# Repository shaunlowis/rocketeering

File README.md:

# rocketeering
Documentation, progress and updates added [here](https://shaunlowis.github.io/rocketeering/)

NOTE: This guide, code, information and its authors assume no liability for outcomes or results of its use or distribution. All code and information is provided as-is for education purposes.

# Setup

Download appropriate version from [here](https://sourceforge.net/projects/sdcc/)

## Ubuntu

If on ubuntu, you should already have gcc and some form of python.

```
cd path-to-download

tar xjf sdcc-<some-version>.tar.bz

cd sdcc-<some-version>

# this will contain another file with the same name, move to that:
cd sdcc-<some-version>

# then run:
sudo ./configure

# you will probably have some missing dependencies, which I just installed with:
sudo apt install bison
sudo apt install flex
sudo apt install gputils

# repeat above until all requirements are met
# this will take quite a long time
make

# slightly faster
sudo make install

# if all went well:
sdcc -v

# which outputs something like:
SDCC : mcs51/z80/z180/r2k/r2ka/r3ka/sm83/tlcs90/ez80_z80/z80n/r800/ds390/pic16/pic14/TININative/ds400/hc08/s08/stm8/pdk13/pdk14/pdk15/mos6502/mos65c02 TD- 4.4.0 #14620 (Linux)
published under GNU General Public License (GPL)
```

Note; semi-useful guide on SDCC, see [here](https://martyn.welchs.me.uk/posts/installing-and-using-sdcc-on-linux/). For a more comprehensive guide, see the [user manual](https://sdcc.sourceforge.net/doc/sdccman.pdf).

Now we need to install the STM8 flash setup. I assume you have an ST-Link debugger, with a SWIM capable interface.
```
# wherever you want the repo to be
git clone https://github.com/vdudouyt/stm8flash.git

cd stm8flash

# dependencies:
sudo apt-get install pkg-config libusb-1.0-0-dev

make

sudo make install
```

### Download standard library
Source files for the STM8S Standard Peripheral Library are available from ST,
but it is more recommended to get the patched files from [here](https://github.com/roshbaby/stm8s-sdcc). Some further adjustments are required, depending on the
specific STM8 you have.

### Wiring the STLINK
We are using the STLINK-V2. The STM8 micro has to be debugged over SWIM.

Details for this are in section 7.3.3 [here](https://www.st.com/resource/en/user_manual/um2448-stlinkv3set-debuggerprogrammer-for-stm8-and-stm32-stmicroelectronics.pdf)

For debugging, connect SWO to the SWIM breakout header on the schematic and NRST TO NRST.

You may need to remove writing protection:

```
echo "00 00 ff 00 ff 00 ff 00 ff 00 ff" | xxd -r -p > factory_defaults.bin
stm8flash -c stlinkv2 -p stm8s007c8 -s opt -w factory_defaults.bin
```

## Flashing your first test program onto the STM8

In the `/flight_software` directory, simply do a `make flash` and if all goes well,
the compiled `main.c` file should be flashed onto your microcontroller.

Next up: make a makefile to first compile the stm8s_gpio.h and stm8s_gpio.c and 

## VS Code

Extensions:

- C/C++ for Visual Studio Code
- Hex Editor
- vscode-devdocs

## Possibly a much better setup:
https://github.com/bschwand/STM8-SPL-SDCC

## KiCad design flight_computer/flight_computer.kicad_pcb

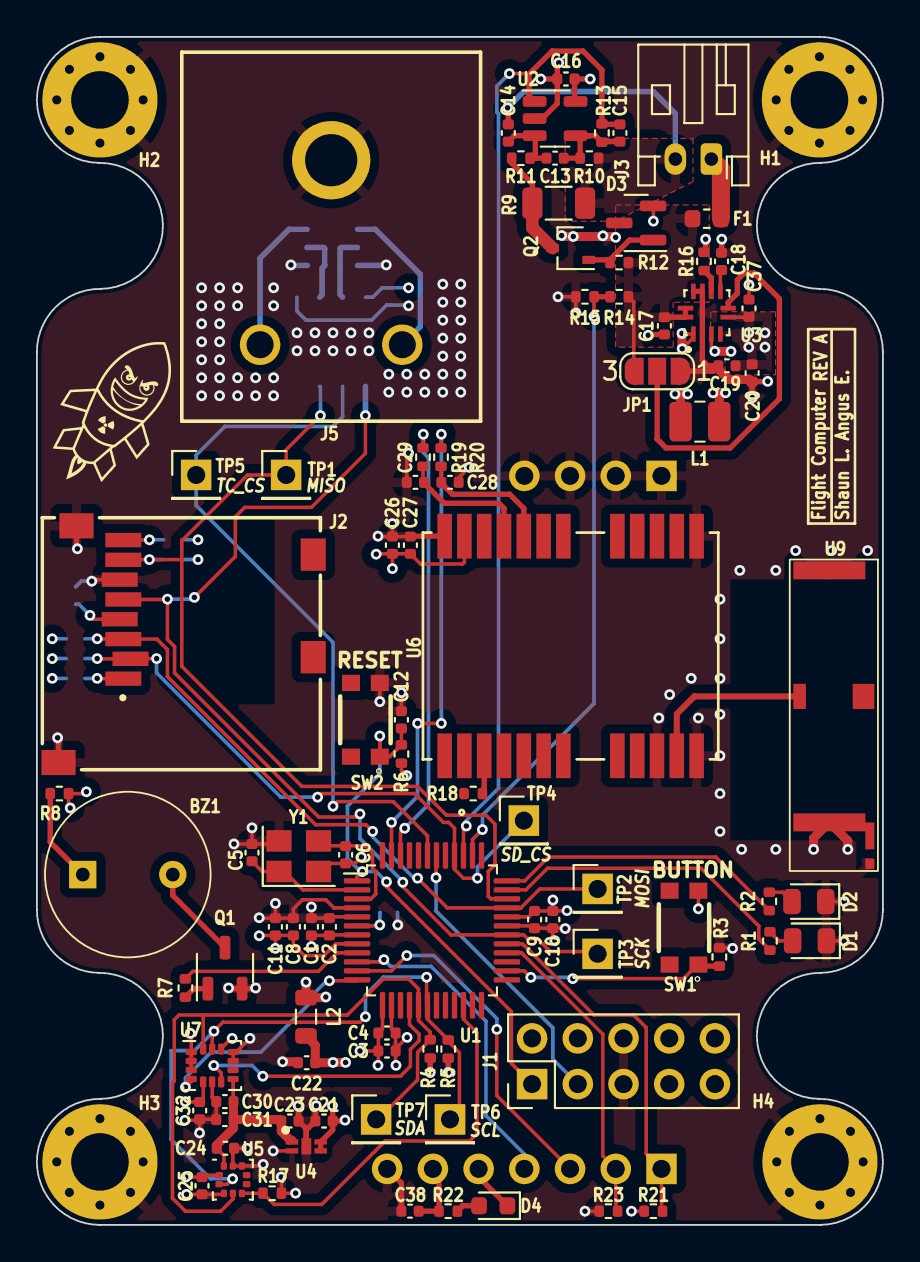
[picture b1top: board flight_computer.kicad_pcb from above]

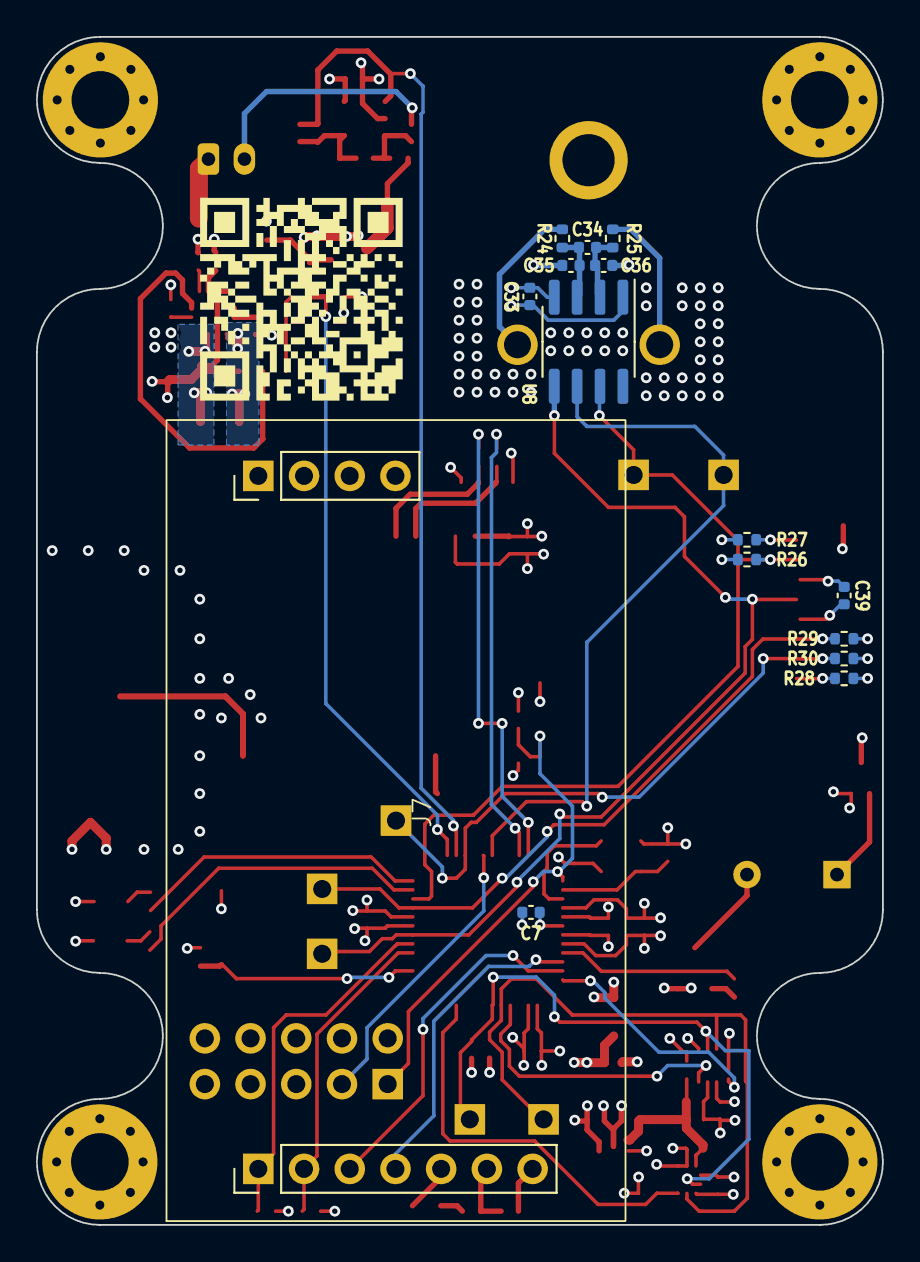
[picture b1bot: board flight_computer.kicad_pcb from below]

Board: 4 copper layers, 47.0 x 66.0 mm, 108 parts (15 on the bottom side), 60 nets.

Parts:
BZ1: Buzzer_indicator; buzzer_Dia9.2mm_P5mm
C1, C3, C10, C11, C17, C19, C20, C22: 10uF; C_0402_1005Metric
C2, C4, C8, C9, C12, C16, C18, C24, C25, C30, C33, C35, C36, C37, C38, C39: 100nF; C_0402_1005Metric
C5, C6: 33pF; C_0402_1005Metric
C7, C21, C23, C34: 1uF; C_0402_1005Metric
C13, C14: 1.8nF; C_0402_1005Metric
C15: 22pF; C_0402_1005Metric
C26, C31: 2.2uF; C_0402_1005Metric
C27, C32: 10nF; C_0402_1005Metric
C28, C29: 100pF; C_0402_1005Metric
D1: Green; LED_0805_2012Metric
D2: Red; LED_0805_2012Metric
D3: 5.1V; SOT-23
D4: Blue; LED_0603_1608Metric
F1: 250mA; Fuse_0603_1608Metric
H1, H2, H3, H4: MountingHole_Pad; MountingHole_3.2mm_M3_Pad_Via
J1: Conn_02x05_Odd_Even; PinHeader_2x05_P2.54mm_Vertical
J2: MEM2061-01-188-00-A_REVA; MEM2061-01-188-00-A
J3: Conn_01x02; JST_PH_S2B-PH-K_1x02_P2.00mm_Horizontal
J5: 3817564
J7: Conn_01x07_MountingPin; E220-400T30D
JP1: PFM; SolderJumper-3_P1.3mm_Open_RoundedPad1.0x1.5mm_NumberLabels
L1: 1.5uH; L_1008_2520Metric
L2: 3.3uH; L_0805_2012Metric
Q1: Q_NPN_BEC; SOT-23-3
Q2: Q_NMOS_GSD; SOT-323_SC-70
R1, R18, R22, R24, R25: 150R; R_0402_1005Metric
R2: 470R; R_0402_1005Metric
R3, R6, R14, R15, R16, R21, R23: 1M; R_0402_1005Metric
R4, R5: 4.7k; R_0402_1005Metric
R7, R10, R11: 1k; R_0402_1005Metric
R8, R19, R20: 0R; R_0402_1005Metric
R9: 0.1R; R_1206_3216Metric
R12, R26, R27, R28, R29, R30: 10k; R_0402_1005Metric
R13: 68k; R_0402_1005Metric
R17: DNP; R_0402_1005Metric
SW1, SW2: SW_Push; KMR2_1
TP1, TP2, TP3, TP4, TP5, TP6, TP7: TestPoint; PinHeader_1x01_P2.54mm_Vertical
U1: STM8S007C8T6TR; LQFP-48_7x7mm_P0.5mm
U2: NCS325; SOT-23-5
U3: TPS63051RMWR; VQFN-12-HR_2.5x2.5mm_P0.5mm
U4: MIC94310-GYMT-TR; TDFN-4-1EP_1.2x1.6mm_P0.5mm
U5: SPL07-003; ST_HLGA-10_2x2mm_P0.5mm_LayoutBorder3x2y
U6: YIC31612EBGG; 24-SMD Module
U7: ICM-42670-P; LGA-14_3x2.5mm_P0.5mm_LayoutBorder3x4y
U8: MAX31855KASA; SOIC-8_3.9x4.9mm_P1.27mm
U9: Antenna_GPS; 1582AT54A0045
Y1: 12MHz; Crystal_SMD_3225-4Pin_3.2x2.5mm

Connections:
/1V8A: C23.1, C24.1, C30.1, C31.1, U4.1 (VOUT), U5.10 (VDDA), U7.8 (VDD)
/GPS_RXD: R19.2, U1.46 (PD5)
/GPS_TXD: R20.2, U1.47 (PD6)
/IMU_FSYNC: U1.16 (PB6), U7.7 (FSYNC)
/IMU_INT: U1.12 (PA6), U7.4 (INT1/INT)
/Microcontroller/3V3D: C1.1, C2.1, C8.1, C9.1, C10.1, C11.1, C19.1, C20.1, C25.1, C26.1, C27.1, C32.1, C33.1, C37.1, C38.1, C39.1, J1.7, J1.8, J2.4 (VDD), J7.6, L2.1, R4.1, R5.1, R6.1, R8.1, R16.1, R22.2, R26.2, R27.2, R28.2, R29.2, R30.2, SW1.2, U1.7 (VDD), U1.8 (VDDIO_1), U1.32 (VDDIO_2), U3.4 (VOUT), U3.5 (FB), U5.1 (VDDIO), U6.23 (VCC), U7.5 (VDDIO), U7.12 (AP_CS), U8.4 (V_CC)
/Microcontroller/BUTTON: R3.1, SW1.1, U1.26 (PC1)
/Microcontroller/BUZZER_INDICATOR: R7.1, U1.9 (PA3)
/Microcontroller/I_{SENSE}: C15.1, R13.2, U1.39 (PE1), U2.1
/Microcontroller/LED_GREEN: R1.1, U1.35 (PG0)
/Microcontroller/LED_RED: R2.1, U1.36 (PG1)
/Microcontroller/NRST: C12.1, J1.1, R6.2, SW2.1, U1.1 (NRST)
/Microcontroller/SPI_MOSI: J2.3 (CMD), R30.1, TP2.1, U1.33 (PC6)
/Microcontroller/SPI_NSS: J2.2 (CD/DAT3), R29.1, TP4.1, U1.40 (PE0)
/Microcontroller/SWIM: J1.3, U1.42 (PD1)
/Microcontroller/VBATT_{SENSE}: R14.2, R15.1, U1.38 (PE2)
/PRESSURE_INT: R17.1, U1.22 (PB0), U5.5 (SDO)
/Power/3V3A: C3.1, C4.1, C16.1, C21.1, C22.1, L2.2, U1.13 (VDDA), U2.5 (V+), U4.3 (EN), U4.4 (VIN)
/Power/BAT_GND: C14.2, J3.2, R9.1, R10.1
/Power/I_{sense_raw}: Q2.3 (D), R9.2, R11.1
/Power/PGOOD: R16.2, U3.8 (PG)
/RADIO_M0: J7.1, R21.2, U1.29 (PC4)
/RADIO_M1: J7.2, R23.2, U1.28 (PC3)
/RADIO_RXD: J7.3, U1.11 (PA5)
/RADIO_TXD: J7.4, U1.10 (PA4)
/Radio/AUX: D4.1 (K), J7.5
/SCL: R5.2, TP6.1, U1.18 (PB4), U5.2 (SCL), U7.13 (AP_SCL/AP_SCLK)
/SDA: R4.2, TP7.1, U1.17 (PB5), U5.4 (SDA), U7.14 (AP_SDA/AP_SDIO/AP_SDI)
/SPI_MISO: J2.7 (DAT0), R26.1, TP1.1, U1.34 (PC7), U8.7 (SO)
/SPI_SCK: J2.5 (CLK), TP3.1, U1.30 (PC5), U8.5 (SCK)
/TC_CS: TP5.1, U1.43 (PD2), U8.6 (~CS)
/Temperature sensor/T+: J5.1, R24.1
/Temperature sensor/T-: J5.2, R25.1
GND: C1.2, C2.2, C3.2, C4.2, C5.1, C6.2, C7.2, C8.2, C9.2, C10.2, C11.2, C12.2, C16.2, C17.2, C18.2, C19.2, C20.2, C21.2, C22.2, C23.2, C24.2, C25.2, C26.2, C27.2, C28.2, C29.2, C30.2, C31.2, C32.2, C33.2, C35.1, C36.2, C37.2, C38.2, C39.2, D1.1 (K), D2.1 (K), D3.2 (A), H1.1, H2.1, H3.1, H4.1, J1.5, J1.6, J2.6 (VSS), J2.11 (GND), J2.12 (GND__1), J5.MH1, J7.7, J7.MP (MountPin), JP1.1 (A), Q1.2 (E), Q2.2 (S), R3.2, R15.2, R17.2, R21.1, R23.1, SW2.2, U1.4 (VSSIO_1), U1.5 (VSS), U1.14 (VSSA), U1.31 (VSSIO_2), U2.2 (V-), U3.2 (GND), U3.9 (GND), U3.10 (ILIM0), U4.2 (GND), U4.5 (EP), U5.3 (GND), U5.8 (GND), U5.9 (GND), U6.10 (GND), U6.12 (GND), U6.13 (GND), U6.24 (GND), U7.1 (AP_SDO/AP_AD0), U7.2 (RESV), U7.3 (RESV), U7.6 (GND), U7.10 (RESV), U7.11 (RESV), U8.1 (GND), U9.2 (GND), U9.4 (GND), U9.5 (CAP), Y1.2, Y1.4
unnamed: BZ1.2 (+), Q1.3 (C)
unnamed: BZ1.1 (-), R8.2
unnamed: D1.2 (A), R1.2
unnamed: D2.2 (A), R2.2
unnamed: D3.1 (K), Q2.1 (G), R12.2
unnamed: D4.2 (A), R22.1
unnamed: J2.8 (DAT1), R27.1
unnamed: J2.1 (DAT2), R28.1
unnamed: F1.1, J3.1
unnamed: C17.1, F1.2, JP1.3 (B), R12.1, R14.1, U3.11 (EN), U3.12 (VIN)
unnamed: JP1.2 (C), U3.6 (PFM/PWM)
unnamed: Q1.1 (B), R7.2
unnamed: C5.2, U1.2 (PA1/OSCIN), Y1.1
unnamed: C6.1, U1.3 (PA2/OSCOUT), Y1.3
unnamed: C7.1, U1.6 (VCAP)
unnamed: C13.2, C14.1, R11.2, U2.3 (+)
unnamed: C13.1, C15.2, R10.2, R13.1, U2.4 (-)
unnamed: L1.2, U3.1 (L1)
unnamed: L1.1, U3.3 (L2)
unnamed: C18.1, U3.7 (SS)
unnamed: R18.2, U6.3 (PPS)
unnamed: U6.11 (RF_IN), U9.1 (Feed)
unnamed: C29.1, R19.1, U6.21 (RXD)
unnamed: C28.1, R20.1, U6.20 (TXD)
unnamed: C34.1, C35.2, R24.2, U8.3 (T+)
unnamed: C34.2, C36.1, R25.2, U8.2 (T-)

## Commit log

2024-04-11 Adding jekyll theme
2024-04-11 update theme and index
2024-04-11 set up site to be able to test locally too.
2024-04-13 testing avionics subpage
2024-04-13 Added subpages, more details on motor design.
2024-04-13 updated index and added home site link
2024-04-21 TODO: revise the calcs used in the sheet for nozzle dims.
2024-04-25 Start of flight computer PCB
2024-04-26 Finished power input design
2024-04-28 MCU circuit started
2024-04-28 Removing backups
2024-04-28 Cubemx changes
2024-04-28 Adding current shunt measurement, amplification, filtering
2024-04-29 Buzzer, LEDs, added actual components for current sensing and others I had missed
2024-04-29 Button
2024-04-29 SD card
2024-04-30 PRessure sensor circuit
2024-05-06 Tidying up schematics and adding most missing sections (Not finished GPS)
2024-05-08 Finishing gps, ready to connect all
2024-05-08 Schematic connecting
2024-05-10 ERC complete
2024-05-10 Part way through review
2024-05-10 Adding shauns thermcoouple
2024-05-10 Test git ignore
2024-05-10 Take 2 for git ignore
2024-05-11 Thermocouple circuit done
2024-05-11 Clean PCb del
2024-05-11 Start of PCB
2024-05-12 testing kicad version compatibility
2024-05-12 KiCAD8 is not compatible with 7: Revert "testing kicad version compatibility"
    This reverts commit 37378f71d3b59c33c1abc1999dff2b71273f3631.
2024-05-16 A hearty attempt at CPU wiring.
2024-05-16 Start of layout
2024-05-18 finsihed grouping the layout
2024-05-19 Layout first effort done
2024-05-19 GPS antenna controlled impedance
2024-05-20 More PCB layout
2024-05-24 Adding E220-400T30D footprint and 3D model
2024-05-24 a routing attempt
2024-05-26 Most of the way through relayout and new antenna
2024-05-26 Antenna routing, and other routing done
2024-05-28 Moving antenna and removing matching circuit
2024-05-28 First draft of PCB routing complete
2024-05-28 DRC gone, not reviews yet
2024-05-28 Most warnings gone now too
2024-05-28 ERC okay
2024-05-29 PCB review done
2024-05-29 revA sent for production
2024-06-03 Some overdue project updates
2024-06-03 see other branches.
2024-07-02 getting SDCC installed
2024-07-03 yet to test new blinky boi
2024-07-05 bit of a mess, but the build is almost working
2024-07-05 checkpointing new structure
2024-07-05 some progress
2024-07-06 promising new folder structure
2024-07-07 ready for testing with different debugger.
2024-07-07 update to gpio mapping
2024-07-11 First program works!
2024-07-11 great big update
2024-07-12 Adding sdcc user manual to readme
2024-07-20 Adding SDCC user manual annotated and some makefile notes
2024-07-20 Raw sdcc make command figured out
2024-07-20 Start of rearranging for my makefile
2024-07-21 working makefile, does not try build the SPL though
2024-07-21 commenting and tidying up
2024-07-21 safety
2024-07-26 Adding flash
2024-07-27 makefile for spl.lib with all files we can use (exceot flash and itc, they break it for some reason)
2024-07-28 spl designed for sdcc, HSI clock setup, delay functions
2024-07-29 uart radio working
2024-08-06 I2C doesnt work
2024-08-09 I2C progress, not working yet
2024-08-10 Working I2C read function
2024-08-12 Fixing makefile + i2c write
2024-08-12 write and verify i2c byte function
2024-08-12 reading something pressure, not quite there tho
2024-08-19 Trying to read coefs but all 0s
2024-08-19 reading coef vals
2024-08-19 copy decoding coefs, untested
2024-08-20 some progress to getting varo data
2024-08-21 Temp calc working, pressure not
2024-08-24 almost fixed 2s compliment
2024-08-24 working 2s compliment and baro reading
2024-08-24 tidying up baro code
2024-08-24 spl07 pressure and temp readings complete, separate I2C module
2024-08-25 no ack from imu
2024-08-26 gps notes
2024-08-27 GPS work
2024-08-28 working IMU init
2024-08-28 working zimu accel read
2024-08-28 Imu working
2024-08-29 start of interrupts
2024-08-29 Uart ISR at least being called
2024-08-30 working int priority, reading gps in int and filling buff
2024-08-31 circbuff for nmea reads preliminary working
2024-08-31 Reading GPS with int into circ buffer based on full msg string
2024-08-31 Working minmea, slightly modified
2024-08-31 sorta working minmea, something wrong with my circ buffer, two messages are trying to be decoded as 1
2024-09-01 buzzer
2024-09-02 some sd card progress
2024-09-02 revert
2024-09-02 SPI working, SD card not fully initing
2024-09-03 SD init working
2024-09-03 Readme
2024-09-05 definitely working SD init at work
2024-09-05 Some petitfs integration
2024-09-05 adding compile error where code is not done so i donmt foreget
2024-09-06 building but nothing runs
2024-09-06 actually building no running
2024-09-07 working gps circbuff
2024-09-07 Sorta working GSA msg
2024-09-09 Tried converting all comments to ansi and compiling with ansi for pff, but it has errors
2024-09-09 trying full fatfs. does not work, same as petitfs
2024-09-10 actual revert
2024-09-10 RX int over radio
2024-09-10 GPS reading and getting for telem
2024-09-10 working imu fosho
2024-09-10 Also working
2024-09-10 Getting all values for telem
2024-09-10 send float raw complete
2024-09-11 some logging progress, not really working :(
2024-09-12 just sending floats over radio is goal
2024-09-15 Some progress with dynamic plots
2024-09-15 plan for better okotting
2024-09-16 sample radio output
2024-09-16 Adding hdop vdop pdop
2024-09-21 radio not workjing
2024-10-08 start of esp32
2024-10-11 To address #7
2024-10-11 RevB PCB work
2024-10-11 SD logging
2024-10-11 Long log test
2024-10-12 adc voltage reading
2024-10-12 got read and write working, need to now parse data.
2024-10-12 battery voltage calibrated
2024-10-18 Both battery voltage and current readings calibrated
2024-10-18 Everything reading, everything logging
2024-10-18 Example log
2024-10-23 Fixed freezing issue #14
2024-11-04 Pretty sure code is right, need to check board.
2024-11-04 software for thermocouple done.
2024-11-05 Addresses #7, for now just leaving as function in main, will move out later.
2024-11-06 TC in its own module. Reading CJC and flags also
2024-11-06 Full code done but freezing issue is back
2024-11-10 found some great textbooks and did estimate of exit temp for thermal model
2024-11-10 made some progress on heat conduction, stopping here for now
2024-11-10 tidying up
2024-11-10 Got basic setup working, need to figure out how to add in stl
2024-11-13 This works for no reason
2024-11-13 Watchdog implemented, and does work but sometimes the reboot gets stuck during GPS init and thus it dies anyway. Initial frezing issue not solved with delay in the circ buff read
2024-11-15 Flight path arc visualisation, point cloud will probably be more useful for real flight data.
2024-11-21 Didnt change shit but seems more reliable
2025-02-10 packing list
2025-02-15 Adding flight log
2025-02-15 log to csv
2025-02-16 analysis
2025-02-21 updated plotting code
2025-02-21 first launch update
2025-02-21 One too many photos!
2025-08-31 Dead reckoning basic
2025-09-06 Animation working
2025-09-06 trajectory gif
2025-09-06 Added basic complementary filter
2025-09-06 Tuned to match video
2025-09-06 better timed gif
